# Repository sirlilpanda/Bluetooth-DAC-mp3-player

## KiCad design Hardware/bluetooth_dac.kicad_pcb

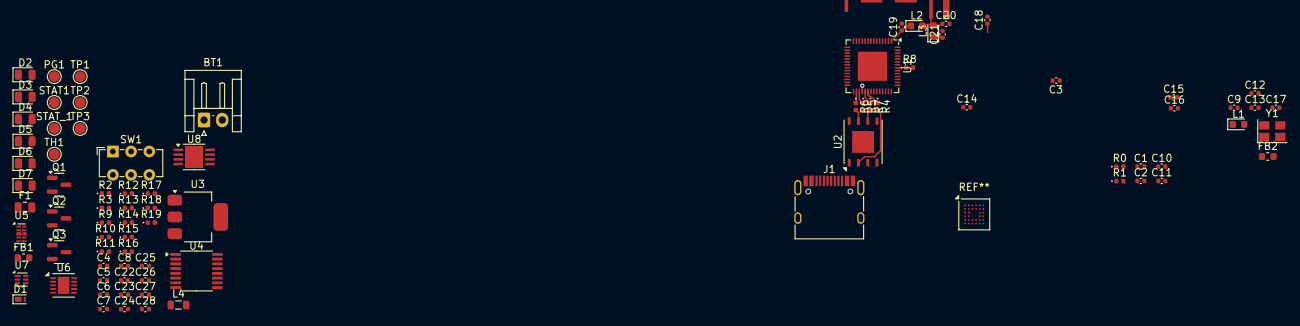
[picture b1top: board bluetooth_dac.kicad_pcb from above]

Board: 2 copper layers, 85 parts (0 on the bottom side), 59 nets.

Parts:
AE1: Antenna; Texas_SWRA117D_2.4GHz_Left
BT1: Battery_Cell; JST_EH_S2B-EH_1x02_P2.50mm_Horizontal
C1, C2, C3, C19, C20, C21, C26: C; C_0402_1005Metric
C4, C5, C6, C7, C11, C22, C23, C27, C28: 10u; C_0402_1005Metric
C8: 100n; C_0402_1005Metric
C9: 10n; C_0402_1005Metric
C10, C12, C17: 1u; C_0402_1005Metric
C13, C14, C15, C16, C18, C24, C25: 0.1u; C_0402_1005Metric
D1: PTVS5V0Z1USK; Nexperia_DSN1608-2_1.6x0.8mm
D2, D4: D_Schottky; D_0805_2012Metric
D3, D5, D6, D7: LED; LED_0805_2012Metric
F1: 2A; Fuse_0805_2012Metric
FB1, FB2: FerriteBead; L_0603_1608Metric
J1: USB_C_Receptacle_USB2.0_14P; USB_C_Receptacle_HRO_TYPE-C-31-M-12
L1, L2, L3: 20nH; LED_0603_1608Metric
L4: 2.2UH3A; L_0805_2012Metric
PG1: TestPoint; TestPoint_Pad_D1.5mm
Q1, Q2, Q3: NMOS; SOT-23
R0, R2, R3, R4, R5, R6, R7: 0; D_0402_1005Metric
R1: TBD; D_0402_1005Metric
R8: 499; D_0402_1005Metric
R9, R10, R11: 470; D_0402_1005Metric
R12: 1k; D_0402_1005Metric
R13: 2k2; D_0402_1005Metric
R14: 330; D_0402_1005Metric
R15, R17: 750k; D_0402_1005Metric
R16, R18: 100k; D_0402_1005Metric
R19: 4.7k; D_0402_1005Metric
STAT1: TestPoint; TestPoint_Pad_D1.5mm
STAT_1: TestPoint; TestPoint_Pad_D1.5mm
SW1: SW_SPST; SW_E-Switch_EG1271_SPDT
TH1: 10K; TestPoint_Pad_D1.5mm
TP1: VDD; TestPoint_Pad_D1.5mm
TP2: VBAT; TestPoint_Pad_D1.5mm
TP3: FEEDBACK; TestPoint_Pad_D1.5mm
U1: ESP32-S3; QFN-56-1EP_7x7mm_P0.4mm_EP4x4mm
U2: MT25QUxxxxxx1xW7; W-PDFN-8-1EP_6x5mm_P1.27mm_EP3x3mm
U3: AMS1117-3.3; SOT-223-3_TabPin2
U4: IP2721; TSSOP-16_4.4x5mm_P0.65mm
U5: ESD224DQA; Diodes_UDFN-10_1.0x2.5mm_P0.5mm
U6: MCP73833-xxx-MF; DFN-10-1EP_3x3mm_P0.5mm_EP1.58x2.35mm
U7: BQ297xy; WSON-6_1.5x1.5mm_P0.5mm
U8: PAM2401; MSOP-8-1EP_3x3mm_P0.65mm_EP2.5x3mm_Mask1.73x2.36mm
Y1: 40MHz; Crystal_SMD_SeikoEpson_TSX3225-4Pin_3.2x2.5mm

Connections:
+3.3V: C3.1, C7.1, C8.1, C10.1, C11.1, C12.1, C13.1, C15.1, C16.1, C17.1, C18.1, FB1.2, FB2.1, L1.1, U1.20 (VDD3P3_RTC), U1.29 (VDD_SPI), U1.46 (VDD3P3_CPU), U2.8 (VCC)
+5V: C27.1, C28.1, D3.2 (A), D4.2 (A), R17.2, U8.7 (OUT)
+BATT: C23.1, C24.1, C25.1, C26.1, F1.1, L4.1, R15.2, TP2.1, U6.9 (V_{BAT}), U6.10 (V_{BAT}), U8.3 (VIN)
/D+: U1.26 (GPIO20/USB_D+), U5.6
/D-: U1.25 (GPIO19/USB_D-), U5.7
/POWER_GOOD: D5.1 (K), D6.1 (K), PG1.1, R10.1, R11.1, STAT1.1, U1.10 (GPIO5), U1.12 (GPIO7)
/SPI_CLK: R7.2, U2.6 (C)
/SPI_CS: U1.32 (SPICS0), U2.1 (~S)
/SPI_D: R0.2, U2.5 (DQ0)
/SPI_HOLD: R6.2, U2.7 (~RESET/DQ3)
/SPI_Q: R4.2, U2.2 (DQ1)
/SPI_W: R5.2, U2.3 (~W/DQ2)
/STAT_1: D7.1 (K), R9.1, STAT_1.1, U1.11 (GPIO6)
GND: C1.2, C2.2, C3.2, C4.2, C5.2, C6.2, C7.2, C8.2, C9.2, C10.2, C11.2, C12.2, C13.2, C14.2, C15.2, C16.2, C17.2, C18.2, C19.2, C20.2, C21.2, C22.2, C23.2, C24.2, C26.2, C27.2, C28.2, D1.2 (A), J1.A1 (GND), J1.A12 (GND), J1.B1 (GND), J1.B12 (GND), Q2.3 (S), R2.2, R3.1, R12.1, R13.1, R16.1, R18.1, R19.1, U1.57 (GND), U2.4 (VSS), U2.9 (PAD), U3.1 (GND), U4.5 (GND), U5.3 (VSS), U5.8 (VSS), U6.5 (V_{SS}), U8.4 (AGND), U8.8 (PGND), Y1.2, Y1.4
GNDS: J1.S1 (SHIELD), R2.1
unnamed: AE1.1 (A), C20.1, L2.2, L3.2
unnamed: BT1.1 (+), SW1.1 (A)
unnamed: BT1.2 (-), Q3.3 (S), R14.1, U7.4 (VSS)
unnamed: C2.1, R1.1, Y1.3
unnamed: C9.1, FB2.2, U1.55 (VDDA), U1.56 (VDDA)
unnamed: C14.1, L1.2, U1.2 (VDD3P3), U1.3 (VDD3P3)
unnamed: C21.1, L3.1
unnamed: C4.1, D1.1 (K), J1.A4 (VBUS), J1.A9 (VBUS), J1.B4 (VBUS), J1.B9 (VBUS), Q1.1 (D), U4.2 (VIN)
unnamed: C6.1, D2.1 (K), D4.1 (K), U3.3 (VI)
unnamed: D3.1 (K), R19.2
unnamed: J1.A5 (CC1), U5.1
unnamed: J1.B5 (CC2), U5.2
unnamed: J1.A6 (D+), J1.B6 (D+), U5.5
unnamed: J1.A7 (D-), J1.B7 (D-), U5.4
unnamed: Q1.2 (G), U4.1 (VBUSG)
unnamed: Q2.1 (D), Q3.1 (D)
unnamed: Q2.2 (G), U7.2 (Cout)
unnamed: Q3.2 (G), U7.3 (Dout)
unnamed: F1.2, SW1.2 (B)
unnamed: C19.1, L2.1, U1.1 (LNA_IN)
unnamed: R7.1, U1.33 (SPICLK)
unnamed: R0.1, U1.35 (SPID)
unnamed: R6.1, U1.30 (SPIHD)
unnamed: R4.1, U1.34 (SPIQ)
unnamed: R5.1, U1.31 (SPIWP)
unnamed: R8.1, U1.49 (U0TXD)
unnamed: C1.1, U1.53 (XTAL_N), Y1.1
unnamed: R1.2, U1.54 (XTAL_P)
unnamed: FB1.1, U3.2 (VO)
unnamed: U4.13 (CC1), U5.10
unnamed: U4.12 (CC2), U5.9
unnamed: R3.2, U4.11 (SEL)
unnamed: R12.2, U6.6 (PROG)
unnamed: R9.2, U6.3 (STAT1)
unnamed: R10.2, U6.4 (STAT2)
unnamed: TH1.1, U6.8 (THERM)
unnamed: R11.2, U6.7 (~PG)
unnamed: C25.2, R14.2, U7.5 (BAT)
unnamed: R13.2, U7.6 (V-)
unnamed: R15.1, U8.2 (EN)
unnamed: R17.1, R18.2, TP3.1, U8.5 (FB)
unnamed: L4.2, U8.1 (LX)
unnamed: R16.2, U8.6 (RSET)
VBUS: C5.1, C22.1, D2.2 (A), D5.2 (A), D6.2 (A), D7.2 (A), Q1.3 (S), TP1.1, U4.16 (VBUS), U6.1 (V_{DD}), U6.2 (V_{DD})

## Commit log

2024-10-22 init
2024-10-22 pdf of sch
